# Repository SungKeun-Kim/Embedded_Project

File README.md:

# Embedded Projects

임베디드 프로젝트 통합 저장소

## 프로젝트 구조

```
06_Embeded_Proj/
├── kicad/      # KiCad 회로 설계 프로젝트
├── avr/        # AVR/ATtiny/Arduino 펌웨어
└── stm32/      # STM32 펌웨어 프로젝트
```

## 버전 관리

- Git을 사용한 통합 버전 관리
- 각 하위 폴더별 독립적인 .gitignore 설정
- 프로젝트별 README.md 문서화

## 작성일

2025.12.04

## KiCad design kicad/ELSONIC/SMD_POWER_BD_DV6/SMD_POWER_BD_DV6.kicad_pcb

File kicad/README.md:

# KiCad 프로젝트

회로 설계 및 PCB 레이아웃 프로젝트

## 프로젝트 목록

- (POWER_BD_SV2.0:SMD 버젼 2026.02.24)

## 사용 도구

- KiCad 9.0

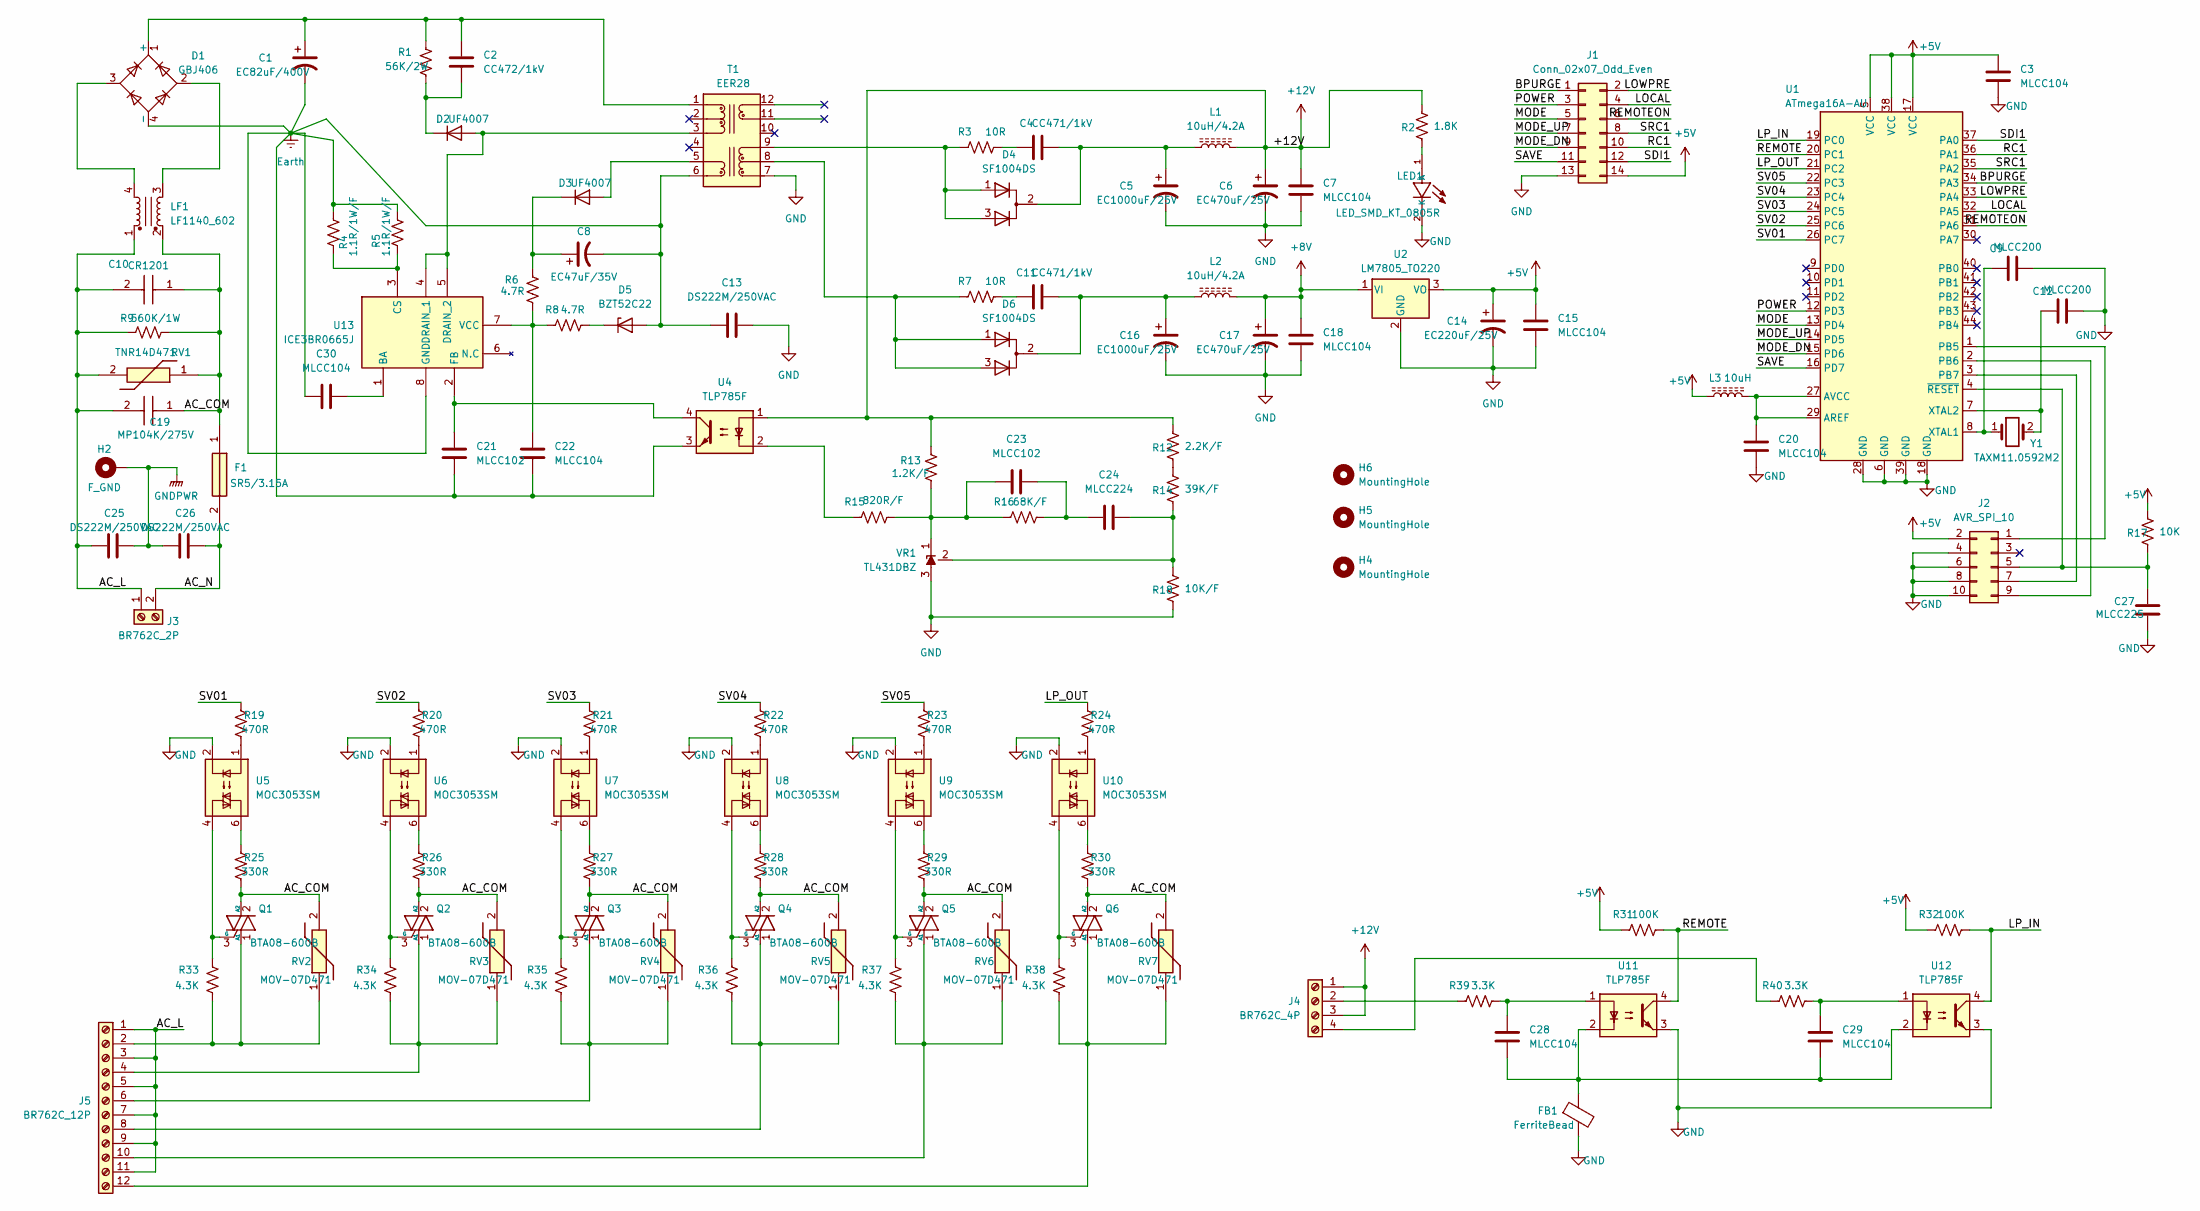
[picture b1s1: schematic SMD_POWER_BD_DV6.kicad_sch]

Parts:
C1: EC82uF/400V; 82uF_400V
C2: CC472/1kV; C_3216Metric; LCSC C9192
C3, C7, C15, C18, C20, C22, C28, C29, C30: MLCC104; C_3216Metric; LCSC C24497
C4, C11: CC471/1kV; C_3216Metric; LCSC C9189
C5, C16: EC1000uF/25V; CP_Radial_D10.0mm_P5.00mm
C6, C17: EC470uF/25V; CP_Radial_D10.0mm_P5.00mm
C8: EC47uF/35V; CP_Elec_6.3x5.4; LCSC C970678
C9, C12: MLCC200; C_3216Metric; LCSC C377026
C10: CR1201; SPARK_KILLER
C13, C25, C26: DS222M/250VAC; DS222M
C14: EC220uF/25V; CP_Elec_6.3x7.7; LCSC C2992606
C19: MP104K/275V; 104K_275V
C21, C23: MLCC102; C_3216Metric; LCSC C1941
C24: MLCC224; C_3216Metric; LCSC C1857
C27: MLCC225; C_3216Metric; LCSC C107183
D1: GBJ406
D2, D3: UF4007; D_SMA; LCSC C81191
D4, D6: SF1004DS; TO-252-2; LCSC C3011035
D5: BZT52C22; D_SOD-123; LCSC C2108
F1: SR5/3.15A; SR525ABK
FB1: FerriteBead; R_Axial_0.25W_P10.16mm
H2: F_GND; MTHole_3.5mm_7.5mmPad_GND
H4, H6: MountingHole; MTHole_3.5mm
H5: MountingHole; MTHole_3.5mm_ANTICOPPER
J1: Conn_02x07_Odd_Even; IDC-Header_2x07_P2.54mm_Vertical
J2: AVR_SPI_10; IDC-Header_2x05_P2.54mm_Vertical
J3: BR762C_2P; BR762_02P
J4: BR762C_4P; BR762_04P
J5: BR762C_12P; BR762_12P
L1, L2: 10uH/4.2A; L_Sumida_CDMC6D28_7.25x6.5mm; LCSC C436542
L3: 10uH; R_3216Metric; LCSC C412018
LED1: LED_SMD_KT_0805R; LED_2012Metric; LCSC C2295
LF1: LF1140_602; LF1140
Q1, Q2, Q3, Q4, Q5, Q6: BTA08-600B; TO-220-3_Vertical
R1: 56K/2W; R_Axial_2W_P20.32mm
R2: 1.8K; R_3216Metric; LCSC C102291
R3, R7: 10R; R_4532Metric; LCSC C2933875
R4, R5: 1.1R/1W/F; R_6332Metric; LCSC C5154651
R6, R8: 4.7R; R_3216Metric; LCSC C104836
R9: 560K/1W; R_Axial_1W_P14.6mm
R12: 2.2K/F; R_3216Metric; LCSC C140044
R13: 1.2K/F; R_3216Metric; LCSC C104614
R14: 39K/F; R_3216Metric; LCSC C18008
R15: 820R/F; R_3216Metric; LCSC C17984
R16: 68K/F; R_3216Metric; LCSC C137239
R17: 10K; R_3216Metric; LCSC C136460
R18: 10K/F; R_3216Metric; LCSC C17902
R19, R20, R21, R22, R23, R24: 470R; R_3216Metric; LCSC C104820
R25, R26, R27, R28, R29, R30: 330R; R_3216Metric; LCSC C414913
R31, R32: 100K; R_3216Metric; LCSC C127274
R33, R34, R35, R36, R37, R38: 4.3K; R_3216Metric; LCSC C2759585
R39, R40: 3.3K; R_3216Metric; LCSC C168540
RV1: TNR14D471; TNR14D_P7.62
RV2, RV3, RV4, RV5, RV6, RV7: MOV-07D471; C_Disc_D8.0mm_W4.8mm_P5.00mm
T1: EER28; EER28_35_12P
U1: ATmega16A-AU; TQFP-44_10x10mm_P0.8mm; LCSC C5658
U2: LM7805_TO220; TO-252-2; LCSC C21706
U4, U11, U12: TLP785F; SOP-4_7.5x4.1mm_P2.54mm; LCSC C45445
U5, U6, U7, U8, U9, U10: MOC3053SM; SOIC-6_P2.54mm-CUTLINE; LCSC C22469445
U13: ICE3BR0665J; DIP-8_W7.62mm_Socket
VR1: TL431DBZ; SOT-23-3; LCSC C23892
Y1: TAXM11.0592M2; Crystal_SMD_HC49-SD; LCSC C362349

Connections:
+5V: C3.2, C14.1, C15.2, J1.14, J2.2, L3.1, R17.2, R31.1, R32.1, U1.5 (VCC), U1.17 (VCC), U1.38 (VCC), U2.3 (VO)
+8V: C17.1, C18.2, L2.2, U2.1 (VI)
+12V: C6.1, C7.2, J4.1, J4.3, L1.2, R2.2, R12.2, R13.2, U4.1
/AC_COM: C10.1, C19.1, F1.1, LF1.2, Q1.2 (A2), Q2.2 (A2), Q3.2 (A2), Q4.2 (A2), Q5.2 (A2), Q6.2 (A2), R9.2, R25.1, R26.1, R27.1, R28.1, R29.1, R30.1, RV1.1, RV2.2, RV3.2, RV4.2, RV5.2, RV6.2, RV7.2
/AC_L: C10.2, C19.2, C25.1, J3.1, J5.1, J5.3, J5.5, J5.7, J5.9, J5.11, LF1.1, R9.1, RV1.2
/AC_N: C26.2, F1.2, J3.2
/BPURGE: J1.1, U1.34 (PA3)
/LOCAL: J1.4, U1.32 (PA5)
/LOWPRE: J1.2, U1.33 (PA4)
/LP_IN: R32.2, U1.19 (PC0), U12.4
/LP_OUT: R24.2, U1.21 (PC2)
/MODE: J1.5, U1.13 (PD4)
/MODE_DN: J1.9, U1.15 (PD6)
/MODE_UP: J1.7, U1.14 (PD5)
/POWER: J1.3, U1.12 (PD3)
/RC1: J1.10, U1.36 (PA1)
/REMOTE: R31.2, U1.20 (PC1), U11.4
/REMOTEON: J1.6, U1.31 (PA6)
/SAVE: J1.11, U1.16 (PD7)
/SDI1: J1.12, U1.37 (PA0)
/SRC1: J1.8, U1.35 (PA2)
/SV01: R19.2, U1.26 (PC7)
/SV02: R20.2, U1.25 (PC6)
/SV03: R21.2, U1.24 (PC5)
/SV04: R22.2, U1.23 (PC4)
/SV05: R23.2, U1.22 (PC3)
Earth: C1.2, C8.2, C13.1, C21.1, C22.1, C30.1, D1.4 (-), D5.2 (A), R4.1, R5.1, T1.6 (Vcc_GND), U4.3, U13.8 (GND)
GND: C3.1, C5.2, C6.2, C7.1, C9.2, C12.2, C13.2, C14.2, C15.1, C16.2, C17.2, C18.1, C20.1, C27.1, FB1.2, J1.13, J2.4, J2.6, J2.8, J2.10, LED1.2 (K), R18.1, T1.7 (N_GND1), U1.6 (GND), U1.18 (GND), U1.28 (GND), U1.39 (GND), U2.2 (GND), U5.2, U6.2, U7.2, U8.2, U9.2, U10.2, U11.3, U12.3, VR1.3 (A)
GNDPWR: C25.2, C26.1, H2.1 (1_1)
unnamed: C4.1, R3.2
unnamed: C11.1, R7.2
unnamed: C23.2, C24.1, R16.2
unnamed: C28.1, C29.1, FB1.1, U11.2, U12.2
unnamed: C28.2, R39.2, U11.1
unnamed: C29.2, R40.2, U12.1
unnamed: C1.1, C2.1, D1.1 (+), R1.1, T1.1 (P0)
unnamed: D1.2, LF1.3
unnamed: D1.3, LF1.4
unnamed: D2.2 (A), T1.3 (P2), U13.4 (DRAIN_1), U13.5 (DRAIN_2)
unnamed: C2.2, D2.1 (K), R1.2
unnamed: D3.2 (A), T1.5 (Vcc)
unnamed: C8.1, D3.1 (K), R6.1
unnamed: C4.2, C5.1, D4.2 (K), L1.1
unnamed: D5.1 (K), R8.2
unnamed: C11.2, C16.1, D6.2 (K), L2.1
unnamed: J2.1, U1.1 (PB5)
unnamed: C27.2, J2.5, R17.1, U1.4 (~RESET)
unnamed: J2.7, U1.3 (PB7)
unnamed: J2.9, U1.2 (PB6)
unnamed: J4.2, R39.1
unnamed: J4.4, R40.1
unnamed: J5.2, Q1.1 (A1), R33.1, RV2.1
unnamed: J5.4, Q2.1 (A1), R34.1, RV3.1
unnamed: J5.6, Q3.1 (A1), R35.1, RV4.1
unnamed: J5.8, Q4.1 (A1), R36.1, RV5.1
unnamed: J5.10, Q5.1 (A1), R37.1, RV6.1
unnamed: J5.12, Q6.1 (A1), R38.1, RV7.1
unnamed: LED1.1 (A), R2.1
unnamed: Q1.3 (G), R33.2, U5.4
unnamed: Q2.3 (G), R34.2, U6.4
unnamed: Q3.3 (G), R35.2, U7.4
unnamed: Q4.3 (G), R36.2, U8.4
unnamed: Q5.3 (G), R37.2, U9.4
unnamed: Q6.3 (G), R38.2, U10.4
unnamed: R12.1, R14.2
unnamed: R15.1, U4.2
unnamed: R19.1, U5.1
unnamed: R20.1, U6.1
unnamed: R21.1, U7.1
unnamed: R22.1, U8.1
unnamed: R23.1, U9.1
unnamed: R24.1, U10.1
unnamed: R25.2, U5.6
unnamed: R26.2, U6.6
unnamed: R27.2, U7.6
unnamed: R28.2, U8.6
unnamed: R29.2, U9.6
unnamed: R30.2, U10.6
unnamed: D6.1 (A), D6.3 (A), R7.1, T1.8 (N1)
unnamed: D4.1 (A), D4.3 (A), R3.1, T1.9 (N2)
unnamed: C20.2, L3.2, U1.27 (AVCC), U1.29 (AREF)
unnamed: C9.1, U1.8 (XTAL1), Y1.1
unnamed: C12.1, U1.7 (XTAL2), Y1.2
unnamed: C30.2, U13.1 (BA)
unnamed: R4.2, R5.2, U13.3 (CS)
unnamed: C21.2, U4.4, U13.2 (FB)
unnamed: C22.2, R6.2, R8.1, U13.7 (VCC)
unnamed: C23.1, R13.1, R15.2, R16.1, VR1.1 (K)
unnamed: C24.2, R14.1, R18.2, VR1.2 (REF)

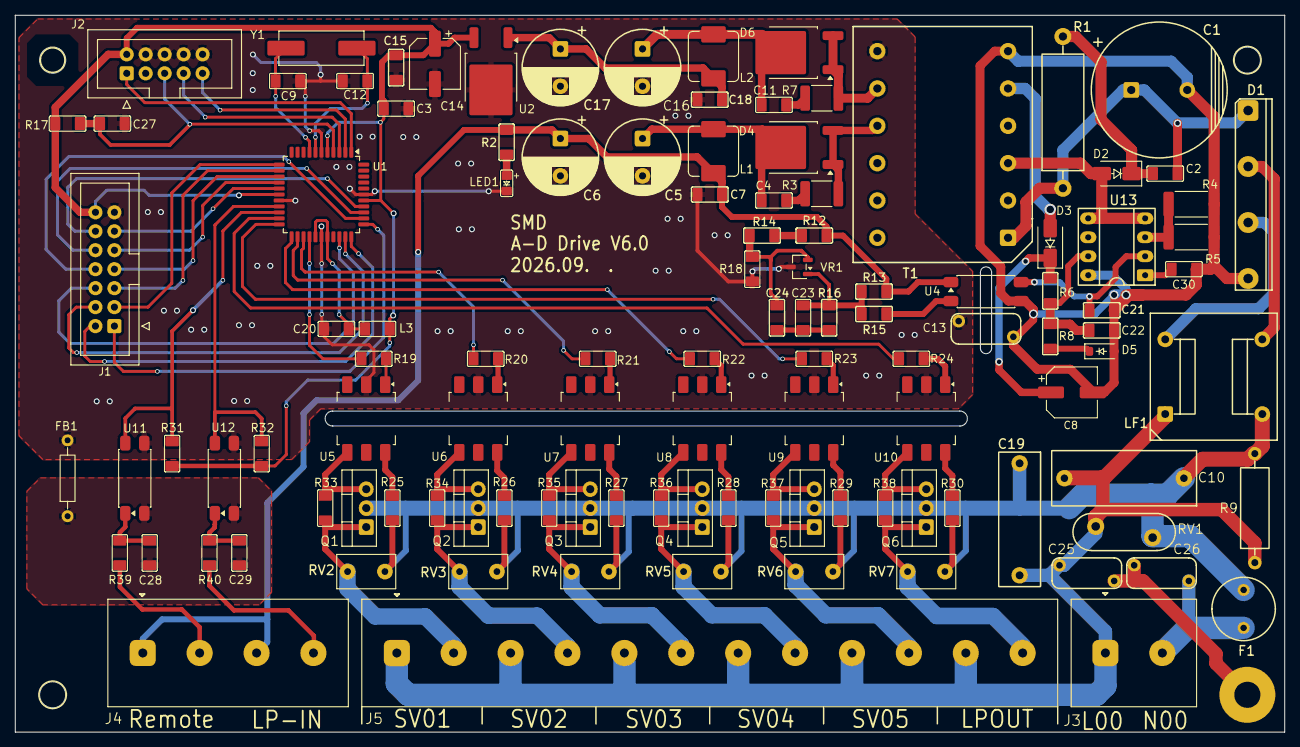
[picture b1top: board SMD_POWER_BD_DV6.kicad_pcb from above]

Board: 2 copper layers, 170.0 x 96.0 mm, 118 parts (0 on the bottom side), 89 nets.

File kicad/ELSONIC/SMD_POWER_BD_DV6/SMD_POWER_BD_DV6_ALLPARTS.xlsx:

| Value | Reference | Footprint | LCSC
1 | MOC3053SM | U5,U6,U7,U8,U9,U10 | 01_MyFoot_ICs:SOIC-6_P2.54mm-CUTLINE | C22469445
2 | 1.1R/1W/F | R4,R5 | 04_MyFoot_Passive:R_6332Metric | C5154651
3 | SF1004DS | D4,D6 | 01_MyFoot_ICs:TO-252-2 | C3011035
4 | EC220uF/25V | C14 | 04_MyFoot_Passive:CP_Elec_6.3x7.7 | C2992606
5 | 10R | R3,R7 | 04_MyFoot_Passive:R_4532Metric | C2933875
6 | 4.3K | R33,R34,R35,R36,R37,R38 | 04_MyFoot_Passive:R_3216Metric | C2759585
7 | EC47uF/35V | C8 | 04_MyFoot_Passive:CP_Elec_6.3x5.4 | C970678
8 | 10uH/4.2A | L1,L2 | 04_MyFoot_Passive:L_Sumida_CDMC6D28_7.25x6.5mm | C436542
9 | 330R | R25,R26,R27,R28,R29,R30 | 04_MyFoot_Passive:R_3216Metric | C414913
10 | 10uH | L3 | 04_MyFoot_Passive:R_3216Metric | C412018
11 | MLCC200 | C9,C12 | 04_MyFoot_Passive:C_3216Metric | C377026
12 | TAXM11.0592M2 | Y1 | 03_MyFoot_Active:Crystal_SMD_HC49-SD | C362349
13 | 3.3K | R39,R40 | 04_MyFoot_Passive:R_3216Metric | C168540
14 | 2.2K/F | R12 | 04_MyFoot_Passive:R_3216Metric | C140044
15 | 68K/F | R16 | 04_MyFoot_Passive:R_3216Metric | C137239
16 | 10K | R17 | 04_MyFoot_Passive:R_3216Metric | C136460
17 | 100K | R31,R32 | 04_MyFoot_Passive:R_3216Metric | C127274
18 | MLCC225 | C27 | 04_MyFoot_Passive:C_3216Metric | C107183
19 | 4.7R | R6,R8 | 04_MyFoot_Passive:R_3216Metric | C104836
20 | 470R | R19,R20,R21,R22,R23,R24 | 04_MyFoot_Passive:R_3216Metric | C104820
21 | 1.2K/F | R13 | 04_MyFoot_Passive:R_3216Metric | C104614
22 | 1.8K | R2 | 04_MyFoot_Passive:R_3216Metric | C102291
23 | UF4007 | D2,D3 | 03_MyFoot_Active:D_SMA | C81191
24 | TLP785F | U4,U11,U12 | 01_MyFoot_ICs:SOP-4_7.5x4.1mm_P2.54mm | C45445
25 | MLCC104 | C3,C7,C15,C18,C20,C22,C28,C29,C30 | 04_MyFoot_Passive:C_3216Metric | C24497
26 | TL431DBZ | VR1 | 01_MyFoot_ICs:SOT-23-3 | C23892
27 | LM7805_TO220 | U2 | 01_MyFoot_ICs:TO-252-2 | C21706
28 | 39K/F | R14 | 04_MyFoot_Passive:R_3216Metric | C18008
29 | 820R/F | R15 | 04_MyFoot_Passive:R_3216Metric | C17984
30 | 10K/F | R18 | 04_MyFoot_Passive:R_3216Metric | C17902
31 | CC472/1kV | C2 | 04_MyFoot_Passive:C_3216Metric | C9192
32 | CC471/1kV | C4,C11 | 04_MyFoot_Passive:C_3216Metric | C9189
33 | ATmega16A-AU | U1 | 00_MyFoot_MCU:TQFP-44_10x10mm_P0.8mm | C5658
34 | LED_SMD_KT_0805R | LED1 | 03_MyFoot_Active:LED_2012Metric | C2295
35 | BZT52C22 | D5 | 03_MyFoot_Active:D_SOD-123 | C2108
36 | MLCC102 | C21,C23 | 04_MyFoot_Passive:C_3216Metric | C1941
37 | MLCC224 | C24 | 04_MyFoot_Passive:C_3216Metric | C1857
38 | ICE3BR0665J | U13 | 01_MyFoot_ICs:DIP-8_W7.62mm_Socket
39 | EER28 | T1 | 04_MyFoot_Passive:EER28_35_12P
40 | MOV-07D471 | RV2,RV3,RV4,RV5,RV6,RV7 | 04_MyFoot_Passive:C_Disc_D8.0mm_W4.8mm_P5.00mm
41 | TNR14D471 | RV1 | 04_MyFoot_Passive:TNR14D_P7.62
42 | 560K/1W | R9 | 04_MyFoot_Passive:R_Axial_1W_P14.6mm
43 | 56K/2W | R1 | 04_MyFoot_Passive:R_Axial_2W_P20.32mm
44 | BTA08-600B | Q1,Q2,Q3,Q4,Q5,Q6 | 03_MyFoot_Active:TO-220-3_Vertical
45 | LF1140_602 | LF1 | 04_MyFoot_Passive:LF1140
46 | BR762C_12P | J5 | 02_MyFoot_Connectors:BR762_12P
47 | BR762C_4P | J4 | 02_MyFoot_Connectors:BR762_04P
48 | BR762C_2P | J3 | 02_MyFoot_Connectors:BR762_02P
49 | AVR_SPI_10 | J2 | 02_MyFoot_Connectors:IDC-Header_2x05_P2.54mm_Vertical
50 | Conn_02x07_Odd_Even | J1 | 02_MyFoot_Connectors:IDC-Header_2x07_P2.54mm_Vertical
51 | FerriteBead | FB1 | 04_MyFoot_Passive:R_Axial_0.25W_P10.16mm
52 | SR5/3.15A | F1 | 05_MyFoot_Others:SR525ABK
53 | GBJ406 | D1 | 03_MyFoot_Active:GBJ406
54 | MP104K/275V | C19 | 04_MyFoot_Passive:104K_275V
55 | DS222M/250VAC | C13,C25,C26 | 04_MyFoot_Passive:DS222M
56 | CR1201 | C10 | 04_MyFoot_Passive:SPARK_KILLER
57 | EC470uF/25V | C6,C17 | 04_MyFoot_Passive:CP_Radial_D10.0mm_P5.00mm
58 | EC1000uF/25V | C5,C16 | 04_MyFoot_Passive:CP_Radial_D10.0mm_P5.00mm
59 | EC82uF/400V | C1 | 04_MyFoot_Passive:82uF_400V

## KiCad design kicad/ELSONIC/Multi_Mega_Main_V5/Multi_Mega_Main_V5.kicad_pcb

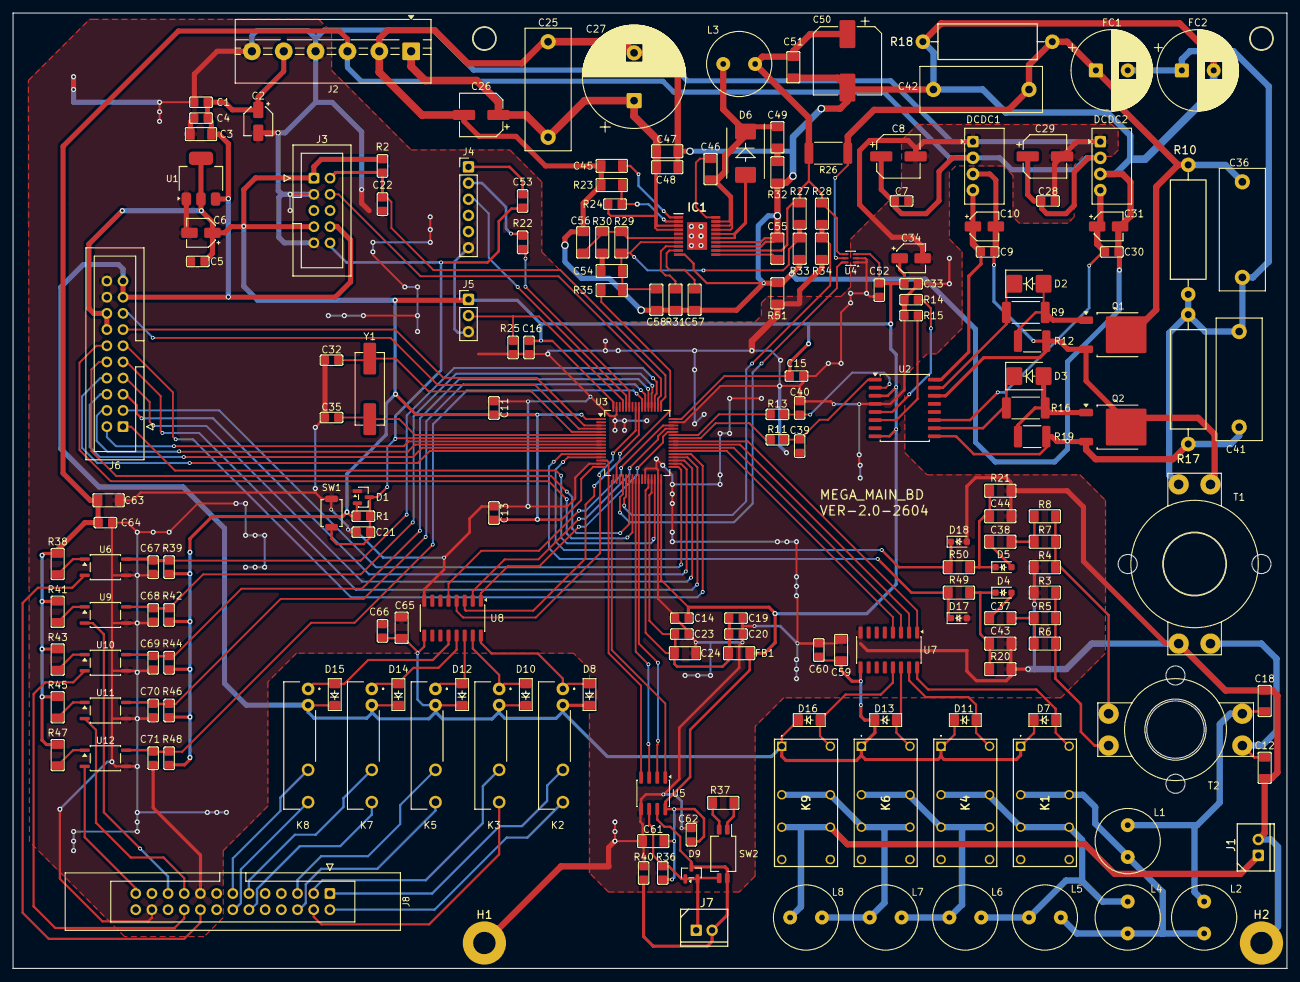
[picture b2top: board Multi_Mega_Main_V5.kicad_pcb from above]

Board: 2 copper layers, 200.0 x 150.0 mm, 193 parts (0 on the bottom side), 130 nets.

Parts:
C1, C4, C5, C7, C9, C11, C13, C14, C15, C16, C19, C21, C23, C28, C30, C33, C52, C53, C60, C62, C64, C66: CL21B104K; C_2012Metric
C2, C6, C10, C31, C34: 10UF25V67RV; CP_Elec_4x5.4
C3, C24, C59, C65: CL31B106K; C_3216Metric
C8, C29: 47UF50V67RV; CP_Elec_6.3x7.7
C12, C18: CG100J; C_3216Metric
C20: CL21B475K; C_2012Metric
C22: CL21C101J; C_2012Metric
C25, C36, C41: 0.1uF100V; C_Rect_W7.0mm_P15.00mm
C26: 10UF100V67RV; CP_Elec_6.3x7.7
C27: 1000UF63V; CP_Radial_D16.0mm_P7.50mm
C32, C35: CG330J; C_2012Metric
C37, C38, C43, C44: CL31B104K; C_3216Metric
C39, C40: CG220J; C_2012Metric
C42: 1uF100V; C_Rect_W7.0mm_P15.00mm
C45: 1206B105K101NT; C_3216Metric
C46: 1206B223K101NT; C_3216Metric
C47, C48: CL31B225K; C_3216Metric
C49, C57: 1206CG331J101NT; C_3216Metric
C50: 220UF50V67RV; CP_Elec_10x10.5
C51: CL31A106K; C_3216Metric
C54, C58: 1206B103K; C_3216Metric
C55: 1206CG102J101NT; C_3216Metric
C56: 1206CG101J; C_3216Metric
C61, C63: CL31B105K; C_3216Metric
C67, C68, C69, C70, C71: CL21B472K; C_2012Metric
D1: BAV99; SOT-23
D2, D3: SS24B; D_SMB
D4, D5: BAT54WSQ-7; D_SOD-323_HandSoldering
D6: B3100-13-F; B3100_13_F
D7, D8, D10, D11, D12, D13, D14, D15, D16: LL4148; LL4148_MELF
D9: SM712-LF-T7; SOT-23
D17, D18: MM3Z3V6; D_SOD-323_HandSoldering
DCDC1, DCDC2: MUS2415N
FB1: CBG321609U; R_3216Metric
FC1, FC2: 470UF63V; CP_Radial_D12.5mm_P5.00mm
H1, H2: MountingHole_Pad; MTHole_3.5mm_6.8mmPad_GND
H3, H4: MountingHole; MTHole_3.5mm
IC1: LM5005MHX_NOPB; SOP65P640X110-21N
J1, J7: SMW250-02P; SMW250_02P
J2: Screw_Terminal_01x06; TB_P5.00mm_6P
J3: ARM_SWD_10; IDC-Header_2x05_P2.54mm_Vertical
J4: Conn_01x06_HEADERPIN; PinHeader_1x06_P2.54mm_Vertical
J5: Conn_01x03; PinHeader_1x03_P2.54mm_Vertical
J6: Conn_02x10_Odd_Even; IDC-Header_2x10_P2.54mm_Vertical
J8: Conn_02x13_Odd_Even; IDC-Header_2x13_P2.54mm_Latch_Vertical
K1, K4, K6, K9: G6A274; G6A274PST15USDC12
K2, K3, K5, K7, K8: PA1A_5V; PA1A5V
L1: 3.3uH; L_Radial_D10.0mm_P5.00mm
L2: 3.9uH; L_Radial_D10.0mm_P5.00mm
L3: 33uH; L_Radial_D10.0mm_P5.00mm
L4: 1.5uH; L_Radial_D10.0mm_P5.00mm
L5: 2.2uH; L_Radial_D10.0mm_P5.00mm
L6: 2.7uH; L_Radial_D10.0mm_P5.00mm
L7: 4.7uH; L_Radial_D10.0mm_P5.00mm
L8: 6.8uH; L_Radial_D10.0mm_P5.00mm
Q1, Q2: STD25N10F7; TO-252-2
R1, R2, R14, R25, R39, R42, R44, R46, R48: W8J0103; R_2012Metric
R3, R4: AR06CTC0500; R_3216Metric
R5, R6, R7, R8: W4F4700; R_3216Metric
R9, R16: 25121WF470; R_6332Metric
R10, R17: 15K/3W; R_Axial_2W_P20.32mm
R11, R13: 0805FR-0747RL; R_2012Metric
R12, R19: 1812J103; R_4532Metric
R15: 0805FR-07100K; R_2012Metric
R18: 22K/3W; R_Axial_2W_P20.32mm
R20, R21, R34: W4F1002; R_3216Metric
R22: 0805FR-0733RL; R_2012Metric
R23: W4J0123; R_3216Metric
R24: W4J0334; R_2012Metric
R26: FRL2512FR047TS-47mohm; R_2512_6332Metric
R27: W4F7502; R_3216Metric
R28: W4F9102; R_3216Metric
R29: W4J0223; R_3216Metric
R30: W4F4992; R_3216Metric
R31: W4J0333; R_3216Metric
R32: W4J0100; R_3216Metric
R33: W4F4991; R_3216Metric
R35: W4F8871; R_3216Metric
R36, R40: W8J0431; R_2012Metric
R37: W4J0121; R_3216Metric
R38, R41, R43, R45, R47: W4J0472; R_3216Metric
R49, R50: W4J0102; R_3216Metric
R51: W4F0000; R_3216Metric
SW1: TS-1088; SW_SPST_TS-1088-xR025
SW2: DSHP02T; CHS-02B_W7.62mm_P1.27mm
T1: TOROID_OUTPUT_OD20_T6T12; Toroid_OD20mm_ID10-T6T12
T2: TOROID_CT_OD16_T1T20; Toroid_OD16mm_ID9.6-T1T20
U1: AMS1117-3.3; SOT-223-3_TabPin2
U2: UCC21520DWR; SOIC-16W_7.5x10.3mm_P1.27mm
U3: STM32G474RBT6; LQFP-64_10x10mm_P0.5mm
U4: INA190A3IDCKR; SOT-363_SC-70-6
U5: MAX3485ESA; SOIC-8_3.9x4.9mm_P1.27mm
U6, U9, U10, U11, U12: TLP185GB-S; SOIC-4_4.55x3.7mm_P2.54mm
U7, U8: ULN2003ADR; SOIC-16_3.9x9.9mm_P1.27mm
Y1: X49SM8M; Crystal_SMD_HC49-SD

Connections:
+3.3V: C5.2, C6.1, C11.2, C13.2, C14.2, C15.2, C16.2, C33.2, C34.1, C52.2, C61.2, C62.2, D1.2 (A), FB1.1, J3.1, J3.7, J5.1, J6.14, J6.16, R1.2, R2.2, R36.2, R39.2, R42.2, R44.2, R46.2, R48.2, U1.2 (VO), U2.3 (VCCI), U2.8 (VCCI), U3.1 (VBAT), U3.16 (VDD), U3.32 (VDD), U3.48 (VDD), U3.64 (VDD), U4.3 (V+), U5.8 (VCC)
+5V: C1.2, C2.1, C3.2, C4.2, C59.2, C60.2, C65.2, C66.2, D7.1 (K), D8.1 (K), D10.1 (K), D11.1 (K), D12.1 (K), D13.1 (K), D14.1 (K), D15.1 (K), D16.1 (K), J2.5, J3.8, J6.17, J6.19, K1.1 (COIL+), K2.2 (++), K3.2 (++), K4.1 (COIL+), K5.2 (++), K6.1 (COIL+), K7.2 (++), K8.2 (++), K9.1 (COIL+), U1.3 (VI), U7.9 (COM), U8.9 (COM)
+15VA: C9.2, C10.1, DCDC1.4 (+Vout), U2.16 (VDDA)
+15VB: C30.2, C31.1, DCDC2.4 (+Vout), U2.11 (VDDB)
+24V: C7.2, C8.1, C28.2, C29.1, C63.2, C64.2, DCDC1.2 (+Vin), DCDC2.2 (+Vin), J2.3, R38.2, R41.2, R43.2, R45.2, R47.2
+48V: C25.2, C26.1, C27.1, C47.2, C48.2, IC1.3 (VIN_1), IC1.4 (VIN_2), J2.1, R24.1
+VBUS: C36.2, C42.2, FC1.1, Q1.2 (D), R10.2, R18.2, R26.1, U4.5 (-)
/ADC1_IN1: D17.1 (K), R49.2, U3.12 (PA0)
/ADC1_IN2: D18.1 (K), R50.2, U3.13 (PA1)
/ADC2_IN3: U3.20 (PA6), U4.6
/ADC2_IN4: R28.1, R34.2, U3.21 (PA7)
/BCD_BIT1: J8.21, U9.3
/BCD_BIT1_M: C68.2, R42.1, U3.52 (PC10), U9.6
/BCD_BIT2: J8.20, U10.3
/BCD_BIT2_M: C69.2, R44.1, U3.53 (PC11), U10.6
/BCD_BIT3: J8.19, U11.3
/BCD_BIT3_M: C70.2, R46.1, U3.54 (PC12), U11.6
/BZ_OUT: J6.12, U3.23 (PC5)
/CHA1: R11.1, U3.42 (PA8)
/CHA2: R13.1, U3.43 (PA9)
/CLK_LCD: J6.13, U3.3 (PC14)
/CLK_LED: J6.15, U3.4 (PC15)
/D0: J6.1, U3.30 (PB10)
/D1: J6.3, U3.33 (PB11)
/D2: J6.5, U3.34 (PB12)
/D3: J6.7, U3.35 (PB13)
/D4: J6.9, U3.36 (PB14)
/D5: J6.11, U3.37 (PB15)
/DAC1_OUT1: R35.2, U3.18 (PA4)
/DE_RS485: U3.24 (PB0), U5.3 (DE)
/DOWN: J6.8, U3.11 (PC3)
/DTR: C53.2, J4.1
/GOING: U3.45 (PA11), U8.2 (I2)
/GOING_A: J8.3, K3.5
/GOING_C: J8.4, K3.6
/HIGH_ALARM: U3.56 (PB3), U8.3 (I3)
/HIGH_ALARM_A: J8.5, K5.5
/HIGH_ALARM_C: J8.6, K5.6
/INA: C39.2, R11.2, U2.1 (INA)
/INB: C40.2, R13.2, U2.2 (INB)
/LC_REL1: U3.38 (PC6), U7.4 (I4)
/LC_REL2: U3.39 (PC7), U7.3 (I3)
/LC_REL3: U3.40 (PC8), U7.2 (I2)
/LC_REL4: U3.41 (PC9), U7.1 (I1)
/LC_RELAY_IN: K1.4 (COM1), K1.13 (COM2), L1.2, L2.2, L4.1, L5.1
/LC_RELAY_OUT: J1.1, K9.6 (NC1), K9.11 (NC2), L8.2
/LOW_ALARM: U3.44 (PA10), U8.1 (I1)
/LOW_ALARM_A: J8.1, K2.5
/LOW_ALARM_C: J8.2, K2.6
/MODE: J6.4, U3.9 (PC1)
/NRST: C21.2, C53.1, D1.3 (K), J3.10, R1.1, SW1.2, U3.7 (PG10)
/REMOTE: J8.18, U6.3
/REMOTE_M: C67.2, R39.1, U3.51 (PA15), U6.6
/SENSOR: J8.25, U12.3
/SENSOR_M: C71.2, R48.1, U3.55 (PD2), U12.6
/SET: J6.10, U3.22 (PC4)
/START_STOP: J6.2, U3.8 (PC0)
/SWCLK: J3.4, U3.50 (PA14)
/SWDIO: C22.2, J3.2, R2.1, U3.49 (PA13)
/TD_ALARM: U3.57 (PB4), U8.4 (I4)
/TD_ALARM_A: J8.11, K7.5
/TD_ALARM_C: J8.12, K7.6
/TOTAL_ALARM: U3.46 (PA12), U8.5 (I5)
/TOTAL_ALARM_A: J8.13, K8.5
/TOTAL_ALARM_C: J8.14, K8.6
/UP: J6.6, U3.10 (PC2)
/USART1_RX: J4.3, U3.60 (PB7)
/USART1_TX: J4.2, R22.2
/USART2_RX: U3.17 (PA3), U5.1 (RO)
/USART2_TX: U3.14 (PA2), U5.4 (DI)
//RE_RS485: U3.25 (PB1), U5.2 (~RE)
GND: C1.1, C2.2, C3.1, C4.1, C5.1, C6.2, C7.1, C8.2, C11.1, C12.1, C13.1, C14.1, C15.1, C16.1, C18.1, C19.1, C20.1, C21.1, C22.1, C23.1, C24.1, C28.1, C29.2, C32.1, C33.1, C34.2, C35.1, C39.1, C40.1, C43.1, C44.1, C52.1, C59.1, C60.1, C61.1, C62.1, C63.1, C64.1, C65.1, C66.1, C67.1, C68.1, C69.1, C70.1, C71.1, D1.1 (K), D17.2 (A), D18.2 (A), DCDC1.1 (-Vin), DCDC2.1 (-Vin), H1.1 (1_1), H2.1 (1_1), J1.2, J2.4, J2.6, J3.3, J3.9, J4.6, J5.3, J6.18, J6.20, J8.17, J8.24, R3.1, R4.1, R14.1, R15.1, R20.1, R21.1, R25.1, R34.1, R40.1, R51.1, SW1.1, T1.4, U1.1 (GND), U2.4 (GND), U3.15 (VSS), U3.27 (VSSA), U3.31 (VSS), U3.47 (VSS), U3.63 (VSS), U4.1 (REF), U4.2 (GND), U5.5 (GND), U6.4, U7.8 (GND), U8.8 (GND), U9.4, U10.4, U11.4, U12.4
GNDA: C9.1, C10.2, DCDC1.3 (-Vout), Q1.3 (S), Q2.2 (D), R12.1, T1.1, U2.14 (VSSA)
GNDB: C25.1, C26.2, C27.2, C30.1, C31.2, C41.1, C42.1, C45.1, C47.1, C48.1, C50.2, C51.1, C55.1, C56.1, C57.1, C58.1, DCDC2.3 (-Vout), FC2.2, IC1.10 (AGND), IC1.13 (PGND_1), IC1.14 (PGND_2), J2.2, Q2.3 (S), R17.1, R18.1, R19.1, R23.2, R31.1, R32.1, R33.1, R51.2, U2.9 (VSSB)
unnamed: C12.2, T1.3, T2.1
unnamed: C18.2, L1.1, L2.1, T2.2
unnamed: C36.1, C41.2, FC1.2, FC2.1, R10.1, R17.2, T1.2
unnamed: C37.2, R5.1, R6.1
unnamed: C38.2, R7.1, R8.1
unnamed: C49.1, R32.2
unnamed: C54.2, R30.1
unnamed: D2.1 (A1), R9.2, U2.15 (OUTA)
unnamed: D2.2 (A2), Q1.1 (G), R9.1, R12.2
unnamed: D3.1 (A1), R16.2, U2.10 (OUTB)
unnamed: D3.2 (A2), Q2.1 (G), R16.1, R19.2
unnamed: C37.1, D4.2 (A)
unnamed: C43.2, D4.1 (K), R20.2, R49.1
unnamed: C38.1, D5.2 (A)
unnamed: C44.2, D5.1 (K), R21.2, R50.1
unnamed: D6.2 (A), IC1.15 (IS_1), IC1.16 (IS_2)
unnamed: C46.1, C49.2, D6.1 (K), IC1.17 (SW_1), IC1.18 (SW_2), IC1.19 (PRE), L3.1
unnamed: D7.2 (A), K1.16 (COIL-), U7.16 (O1)
unnamed: D8.2 (A), K2.1 (-), U8.16 (O1)
unnamed: D9.1 (A1), D9.2 (A2), J7.1, R36.1, SW2.3, U5.6 (A)
unnamed: D9.3 (common), J7.2, R40.2, SW2.4, U5.7 (B)
unnamed: D10.2 (A), K3.1 (-), U8.15 (O2)
unnamed: D11.2 (A), K4.16 (COIL-), U7.15 (O2)
unnamed: D12.2 (A), K5.1 (-), U8.14 (O3)
unnamed: D13.2 (A), K6.16 (COIL-), U7.14 (O3)
unnamed: D14.2 (A), K7.1 (-), U8.13 (O4)
unnamed: D15.2 (A), K8.1 (-), U8.12 (O5)
unnamed: D16.2 (A), K9.16 (COIL-), U7.13 (O4)
unnamed: C46.2, IC1.20 (BST)
unnamed: C56.2, IC1.6 (COMP), R29.2, R30.2
unnamed: C54.1, C58.2, IC1.7 (FB), R27.1, R29.1, R33.2, R35.1
unnamed: C50.1, C51.2, IC1.12 (OUT), L3.2, R26.2, R27.2, R28.2, U4.4 (+)
unnamed: C57.2, IC1.9 (RAMP)
unnamed: IC1.8 (RT), R31.2
unnamed: IC1.2 (SD), R23.1, R24.2
unnamed: C55.2, IC1.11 (SS)
unnamed: C45.2, IC1.1 (VCC)
unnamed: J5.2, R25.2, U3.61 (PB8)
unnamed: K1.6 (NC1), K1.11 (NC2), K4.4 (COM1), K4.13 (COM2), L4.2, L5.2, L6.1
unnamed: K4.6 (NC1), K4.11 (NC2), K6.4 (COM1), K6.13 (COM2), L6.2, L7.1
unnamed: K6.6 (NC1), K6.11 (NC2), K9.4 (COM1), K9.13 (COM2), L7.2, L8.1
unnamed: R3.2, R5.2, R6.2, T2.3
unnamed: R4.2, R7.2, R8.2, T2.4
unnamed: R37.1, SW2.1
unnamed: R37.2, SW2.2
unnamed: R38.1, U6.1
unnamed: R41.1, U9.1
unnamed: R43.1, U10.1
unnamed: R45.1, U11.1
unnamed: R47.1, U12.1
unnamed: R14.2, U2.5 (DIS)
unnamed: R15.2, U2.6 (DT)
unnamed: R22.1, U3.59 (PB6)
unnamed: C32.2, U3.5 (PF0), Y1.2
unnamed: C35.2, U3.6 (PF1), Y1.1
unnamed: C19.2, C20.2, C23.2, C24.2, FB1.2, U3.28 (VREF+), U3.29 (VDDA)

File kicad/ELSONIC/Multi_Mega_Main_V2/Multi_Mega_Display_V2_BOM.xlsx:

Comment | Designator | Footprint | LCSC
CL21B104K | C1,C4,C5,C7,C9,C11,C13,C14,C15,C16,C19,C21,C23,C28,C30,C33,C52,C53,C60,C62,C64,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 | C_2012Metric | C1711
10UF25V67RV | C2,C6,C10,C31,C34 | CP_Elec_4x5.4 | C2895271
CL31B106K | C3,C24,C59,C65 | C_3216Metric | C307369
47UF50V67RV | C8,C29 | CP_Elec_6.3x7.7 | C2887275
CG100J | C12,C18 | C_3216Metric | C1883
CL21B475K | C20 | C_2012Metric | C16194948
CL21C101J | C22 | C_2012Metric | C1790
10UF100V67RV | C26 | CP_Elec_6.3x7.7 | C2895274
CG330J | C32,C35 | C_2012Metric | C157687
CL31B104K | C37,C38,C43,C44 | C_3216Metric | C1945
CG220J | C39,C40 | C_2012Metric | C24658
1206B105K101NT | C45 | C_3216Metric | C91151
1206B223K101NT | C46 | C_3216Metric | C48996
CL31B225K | C47,C48 | C_3216Metric | C39619
1206CG331J101NT | C49,C57 | C_3216Metric | C20617886
220UF50V67RV | C50 | CP_Elec_10x10.5 | C2887271
CL31A106K | C51 | C_3216Metric | C13585
1206B103K | C54 | C_3216Metric | C55077
1206CG102J101NT | C55 | C_3216Metric | C44911
1206CG101J | C56 | C_3216Metric | C1884
1206B103K | C58 | C_3216Metric | C55077
CL31B105K | C61,C63 | C_3216Metric | C13832
CL21B472K | C67,C68,C69,C70,C71 | C_2012Metric | C50131
BAV99 | D1 | SOT-23 | C68983
SS24B | D2,D3 | D_SMB | C35501
BAT54WSQ-7 | D4,D5 | D_SOD-323_HandSoldering | C171824
B3100-13-F | D6 | B3100_13_F | C134447
LL4148 | D7,D8,D10,D11,D12,D13,D14,D15,D16 | LL4148_MELF | C84062
SM712-LF-T7 | D9 | SOT-23 | C2687124
MM3Z3V6 | D17,D18 | D_SOD-323_HandSoldering | C12453
CBG321609U | FB1 | R_3216Metric | C74486
LM5005MHX_NOPB | IC1 | SOP65P640X110-21N | C55575
STD25N10F7 | Q1,Q2 | TO-252-2 | C114860
W8J0103 | R1,R2,R14,R25,R39,R42,R44,R46,R48 | R_2012Metric | C25612
AR06CTC0500 | R3,R4 | R_3216Metric | C5266090
W4F4700 | R5,R6,R7,R8 | R_3216Metric | C4502
25121WF470 | R9,R16 | R_6332Metric | C474195
0805FR-0747RL | R11,R13 | R_2012Metric | C114541
1812J103 | R12,R19 | R_4532Metric | C2933913
0805FR-07100K | R15 | R_2012Metric | C96346
W4F1002 | R20,R21,R34 | R_3216Metric | C17902
0805FR-0733RL | R22 | R_2012Metric | C126353
W4J0123 | R23 | R_3216Metric | C2771295
W4J0334 | R24 | R_2012Metric | C25659
FRL2512FR047TS-47mohm | R26 | R_2512_6332Metric | C7467449
W4F7502 | R27 | R_3216Metric | C17986
W4F9102 | R28 | R_3216Metric | C17981
W4J0223 | R29 | R_3216Metric | C25654
W4F4992 | R30 | R_3216Metric | C18017
W4J0333 | R31 | R_3216Metric | C25660
W4J0100 | R32 | R_3216Metric | C25349
W4F4991 | R33 | R_3216Metric | C57609
W4F8871 | R35 | R_3216Metric | C55354
W8J0431 | R36,R40 | R_2012Metric | C54672
W4J0121 | R37 | R_3216Metric | C25351
W4J0472 | R38,R41,R43,R45,R47 | R_3216Metric | C26043
W4J0102 | R49,R50 | R_3216Metric | C1469
W4F0000 | R51 | R_3216Metric | C17888
TS-1088 | SW1 | SW_SPST_TS-1088-xR025 | C455280
DSHP02T | SW2 | CHS-02B_W7.62mm_P1.27mm | C3293412
AMS1117-3.3 | U1 | SOT-223-3_TabPin2 | C6186
UCC21520DWR | U2 | SOIC-16W_7.5x10.3mm_P1.27mm | C601651
STM32G474RBT6 | U3 | LQFP-64_10x10mm_P0.5mm | C529413
INA190A3IDCKR | U4 | SOT-363_SC-70-6 | C2058578
MAX3485ESA | U5 | SOIC-8_3.9x4.9mm_P1.27mm | C668204
TLP185GB-S | U6,U9,U10,U11,U12 | SOIC-4_4.55x3.7mm_P2.54mm | C388375
ULN2003ADR | U7,U8 | SOIC-16_3.9x9.9mm_P1.27mm | C7512
X49SM8M | Y1 | Crystal_SMD_HC49-SD | C106809

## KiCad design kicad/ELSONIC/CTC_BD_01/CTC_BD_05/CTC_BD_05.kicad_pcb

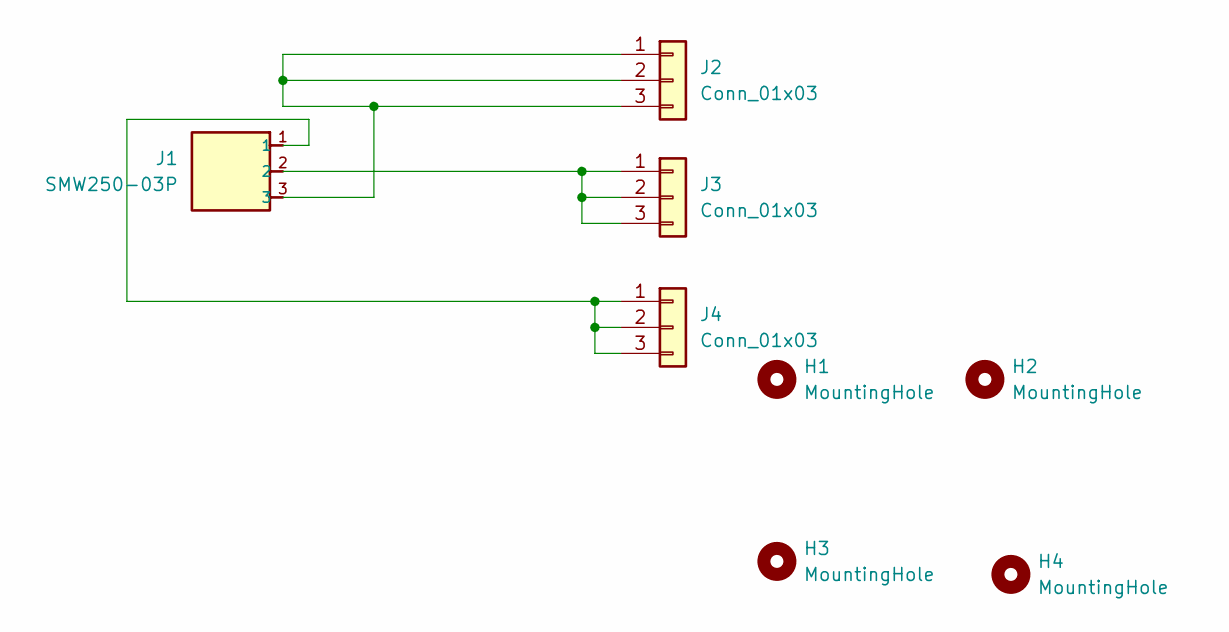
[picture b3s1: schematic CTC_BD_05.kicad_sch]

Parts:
H1, H2: MountingHole; 1.8A
H3, H4: MountingHole; 2.5A
J1: SMW250-03P; SMW250_03P
J2, J3, J4: Conn_01x03; CTC_BK_HALL_01

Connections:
unnamed: J1.3, J2.1, J2.2, J2.3
unnamed: J1.2, J3.1, J3.2, J3.3
unnamed: J1.1, J4.1, J4.2, J4.3

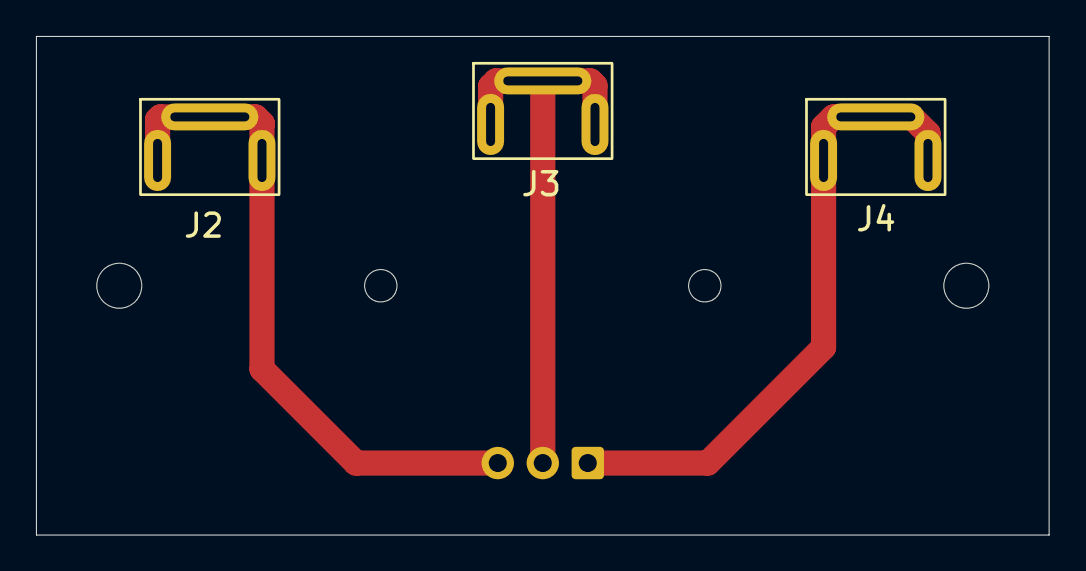
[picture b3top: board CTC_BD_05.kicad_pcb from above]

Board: 2 copper layers, 56.3 x 27.7 mm, 8 parts (1 on the bottom side), 3 nets.
